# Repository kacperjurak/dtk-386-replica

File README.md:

# DTK 386 replica

This is an open source replica of the [DTK PEM-0039U](https://theretroweb.com/motherboards/s/gemlight-gmb-386umc), and its main target was to reverse engineer the pinout and functionality of the UMC 82C491 chipset, for which there are no datasheets online.

Theoretically, it should be fully functional if one were to assemble this, but I do not guarantee there won't be bugs from my side or from the original designers which made it 30+ years ago. The aim was to 100% reproduce the original PCB, with all the original components and footprints, despite the questionable trace routing in certain places.

The gerber files can be found at `/gerber`.

Special thanks to:
- Rigo for providing some useful footprints on his [retro kicad repo](https://github.com/rigred/kicad-retro)
- Sergey for some more useful footprints and symbols, from the [sandy river 486 repo](https://github.com/skiselev/sandy_river_486)

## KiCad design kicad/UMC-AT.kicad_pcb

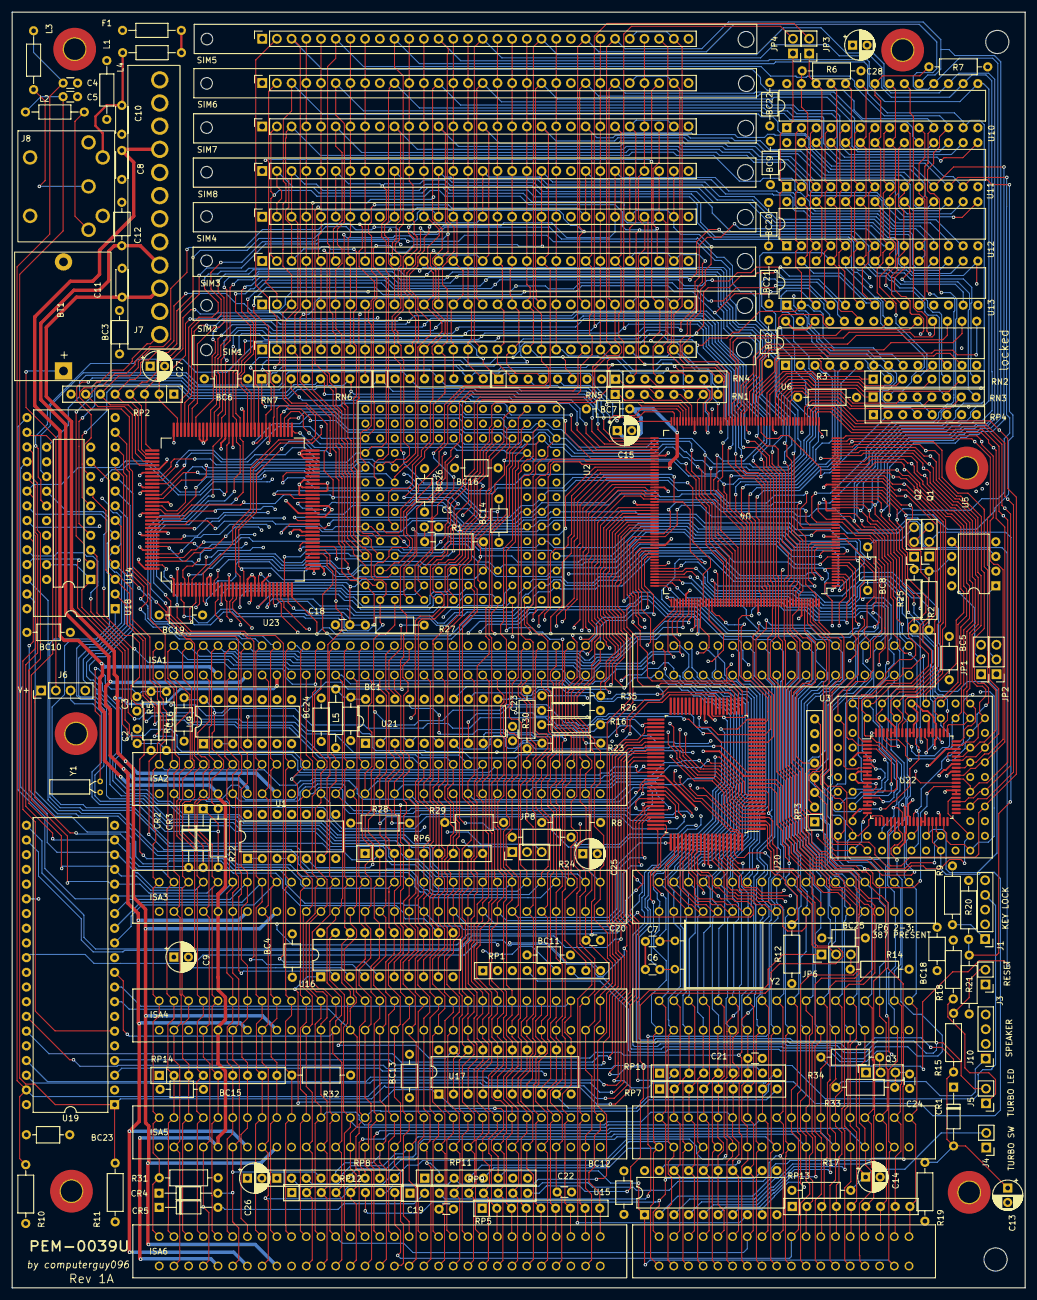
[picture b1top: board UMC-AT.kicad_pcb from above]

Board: 4 copper layers, 175.0 x 220.4 mm, 179 parts (0 on the bottom side), 337 nets.

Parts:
BC1, BC2, BC3, BC4, BC5, BC6, BC7, BC8, BC9, BC10, BC11, BC12, BC13, BC14, BC15, BC16, BC18, BC19, BC20, BC21, BC22, BC23, BC24, BC25, BC26: 100nF; C_Axial_L3.8mm_D2.6mm_P7.50mm_Horizontal
BT1: 3.6V NiCd; BATT
C1, C2, C3, C4, C5, C18, C19, C20, C21, C22, C23, C24: C; C_Disc_D3.0mm_W1.6mm_P2.50mm
C6, C7: 10pF; C_Disc_D3.0mm_W1.6mm_P2.50mm
C8, C10, C11: C; C_Disc_D4.3mm_W1.9mm_P5.00mm
C9, C13, C14, C15, C25, C26, C27, C28: 10uF; CP_Radial_D5.0mm_P2.50mm
C12, C16: C; C_Axial_L3.8mm_D2.6mm_P7.50mm_Horizontal
CR1, CR2, CR3, CR4, CR5: 1N4148; D_DO-35_SOD27_P10.16mm_Horizontal
F1: 1A; L_Axial_L5.3mm_D2.2mm_P10.16mm_Horizontal_Vishay_IM-1
H1, H2, H3, H4, H5, H6: MountingHole_Pad; MountingHole_3.7mm_Pad_TopBottom
ISA1, ISA3, ISA4, ISA5, ISA6: Bus_ISA_16bit; ISA16
ISA2: Bus_ISA_8bit; ISA8
J1: KEY LOCK; PinHeader_1x05_P2.54mm_Vertical
J3: RESET; PinHeader_1x02_P2.54mm_Vertical
J4: TURBO SW; PinHeader_1x02_P2.54mm_Vertical
J5: TURBO LED; PinHeader_1x02_P2.54mm_Vertical
J6: V+; PinHeader_1x04_P2.54mm_Vertical
J7: ATPWR
J8: KB_DIN5
J10: SPEAKER; PinHeader_1x04_P2.54mm_Vertical
JP1, JP2, JP8: PinHeader_1x03_P2.54mm_Vertical
JP3, JP4: PinHeader_1x02_P2.54mm_Vertical
JP6: 387 PRESENT; PinHeader_1x03_P2.54mm_Vertical
L1, L2, L3, L4, L5: FerriteBead; L_Axial_L5.3mm_D2.2mm_P10.16mm_Horizontal_Vishay_IM-1
Q1, Q3: 2N3904; PinSocket_1x03_P2.54mm_Vertical
Q2: 2N3906; PinSocket_1x03_P2.54mm_Vertical
R1, R2, R4, R5, R6, R7, R8, R9, R10, R11, R12, R14, R15, R16, R17, R18, R19, R20, R21, R22, R23, R24, R25, R26, R28, R29, R30, R31, R32, R33, R34, R35: R; R_Axial_DIN0207_L6.3mm_D2.5mm_P10.16mm_Horizontal
R3: 10R; R_Axial_DIN0207_L6.3mm_D2.5mm_P10.16mm_Horizontal
R27: 33R; R_Axial_DIN0207_L6.3mm_D2.5mm_P10.16mm_Horizontal
RN1, RN2, RN3, RN4, RN5, RN6, RN7: 33R; R_Array_SIP8
RP1, RP5, RP6, RP7, RP8, RP9, RP10, RP13, RP14: 4.7K; R_Array_SIP9
RP2, RP3, RP4, RP11, RP12: 4.7K; R_Array_SIP8
SIM1, SIM2, SIM3, SIM4, SIM5, SIM6, SIM7, SIM8: PinSocket_1x30_P2.54mm_Vertical
U1: 74LS00; DIP-14_W7.62mm
U2: 80386; PGA-132
U3: 80387; PGA-68
U4: 82C491; QFP-208
U5: AV9107; DIP-8_W7.62mm
U6, U10, U11, U12, U13: CY62256-70PC; DIP-28_W7.62mm
U9: 4069; DIP-14_W7.62mm
U14, U21: 74LS244; DIP-20_W7.62mm
U15, U16, U17: 74LS245; DIP-20_W7.62mm
U18: 27C512; DIP-28_W15.24mm
U19: DIP-40_W15.24mm
U20: 82C493; QFP-100
U22: Cx87DLC; LQFP-80_14x14mm_P0.65mm
U23: Am386DX; QFP-132
Y1: 32.768KHz; Crystal_C26-LF_D2.1mm_L6.5mm_Horizontal
Y2: 14.318MHz; Crystal_HC49-U_Horizontal

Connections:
+12V: C11.1, ISA1.9 (+12V), ISA2.9 (+12V), ISA3.9 (+12V), ISA4.9 (+12V), ISA5.9 (+12V), ISA6.9 (+12V), J7.10 (+12V)
-5V: C8.2, ISA1.5 (-5V), ISA2.5 (-5V), ISA3.5 (-5V), ISA4.5 (-5V), ISA5.5 (-5V), ISA6.5 (-5V), J7.4 (-5V)
-12V: C12.1, ISA1.7 (-12V), ISA2.7 (-12V), ISA3.7 (-12V), ISA4.7 (-12V), ISA5.7 (-12V), ISA6.7 (-12V), J7.9 (-12V)
/CPU/PULLUP: RP1.7 (R6), U22.27 (PULLUP)
/CPU/READYO: RP3.3 (R2), U3.L3 (~READYO)
/Cache and TAG/AA10: RN2.4 (R2.2), U10.21 (A10), U11.21 (A10), U12.21 (A10), U13.21 (A10)
/Cache and TAG/AA11: RN2.6 (R3.2), U10.23 (A11), U11.23 (A11), U12.23 (A11), U13.23 (A11)
/Cache and TAG/AA13: JP3.1, RP4.5 (R4), U6.8 (A2), U10.26 (A13), U11.26 (A13), U12.26 (A13), U13.26 (A13)
/Cache and TAG/AA14: JP4.1, RP4.4 (R3), U6.7 (A3), U10.1 (A14), U11.1 (A14), U12.1 (A14), U13.1 (A14)
/Cache and TAG/CA2: RN2.3 (R2.1), U4.71 (CA2)
/Cache and TAG/CA3A: RN2.5 (R3.1), U4.70 (CA3A)
/Cache and TAG/COEA: RN2.7 (R4.1), U4.68 (~COEA)
/Cache and TAG/CS0: RN3.4 (R2.2), U10.20 (~CS)
/Cache and TAG/CS1: RN3.6 (R3.2), U11.20 (~CS)
/Cache and TAG/CS2: RN3.8 (R4.2), U12.20 (~CS)
/Cache and TAG/CS3: R3.2, U13.20 (~CS)
/Cache and TAG/CWEA: RN3.1 (R1.1), U4.67 (~CWEA)
/Cache and TAG/OE: R7.1, RN2.8 (R4.2), U10.22 (~OE), U11.22 (~OE), U12.22 (~OE), U13.22 (~OE)
/Cache and TAG/TAG0: U4.83 (TAG0), U6.19 (Q7)
/Cache and TAG/TAG1: U4.82 (TAG1), U6.18 (Q6)
/Cache and TAG/TAG2: U4.81 (TAG2), U6.17 (Q5)
/Cache and TAG/TAG3: U4.80 (TAG3), U6.16 (Q4)
/Cache and TAG/TAG4: U4.79 (TAG4), U6.15 (Q3)
/Cache and TAG/TAG5: U4.77 (TAG5), U6.13 (Q2)
/Cache and TAG/TAG6: U4.76 (TAG6), U6.12 (Q1)
/Cache and TAG/TAG7: U4.75 (TAG7), U6.11 (Q0)
/Cache and TAG/TAGWE: RN2.1 (R1.1), U4.74 (~TAGWE)
/Cache and TAG/TWE: RN2.2 (R1.2), U6.27 (~WE)
/Cache and TAG/WE: R6.1, RN3.2 (R1.2), U10.27 (~WE), U11.27 (~WE), U12.27 (~WE), U13.27 (~WE)
/Chipset/BUFCLK: R28.2, U21.3 (O3b)
/Chipset/CHPCLK: R26.2, U4.141 (ATCLK)
/Chipset/DAC0: U4.116 (DAC0), U20.5 (DAC0)
/Chipset/DAC1: U4.114 (DAC1), U20.6 (DAC1)
/Chipset/DAC2: U4.113 (DAC2), U20.7 (DAC2)
/Chipset/FPUEN: JP6.2, U4.118 (SEL1), U20.3 (SEL1)
/Chipset/JP8/3: JP8.3, U21.16 (O1a)
/Chipset/LOWEN: R35.2, U4.130 (~LOWEN), U20.33 (~LOWEN)
/Chipset/MUXI0: U4.123 (MUXI0), U20.99 (MUXI0)
/Chipset/MUXI1: U4.121 (MUXI1), U20.100 (MUXI1)
/Chipset/MUXI2: U4.120 (MUXI2), U20.1 (MUXI2)
/Chipset/PALE: U4.143 (ALE), U21.11 (I0b)
/Chipset/POWGD: U4.129 (POWGD), U20.34 (POWGD)
/Chipset/RSTIN: U4.171 (~RSTIN), U20.29 (~RSTIN)
/Chipset/SYSCLK: C23.1, R30.1, U20.16 (SYSCLK)
/Chipset/XTL1: C6.2, U20.80 (XTL2), Y2.1
/Chipset/XTL2: C7.2, U20.79 (XTL1), Y2.2
/DRAM/A11: RN4.8 (R4.2), SIM1.24 (A11), SIM2.24 (A11), SIM3.24 (A11), SIM4.24 (A11), SIM5.24 (A11), SIM6.24 (A11), SIM7.24 (A11), SIM8.24 (A11)
/DRAM/CAS0: RN1.4 (R2.2), SIM1.2 (~CAS), SIM1.28 (~CASP), SIM5.2 (~CAS), SIM5.28 (~CASP)
/DRAM/CAS1: RN1.8 (R4.2), SIM2.2 (~CAS), SIM2.28 (~CASP), SIM6.2 (~CAS), SIM6.28 (~CASP)
/DRAM/CAS2: RN4.2 (R1.2), SIM3.2 (~CAS), SIM3.28 (~CASP), SIM7.2 (~CAS), SIM7.28 (~CASP)
/DRAM/CAS3: RN4.4 (R2.2), SIM4.2 (~CAS), SIM4.28 (~CASP), SIM8.2 (~CAS), SIM8.28 (~CASP)
/DRAM/MA0: RN7.2 (R1.2), SIM1.4 (A0), SIM2.4 (A0), SIM3.4 (A0), SIM4.4 (A0), SIM5.4 (A0), SIM6.4 (A0), SIM7.4 (A0), SIM8.4 (A0)
/DRAM/MA1: RN7.4 (R2.2), SIM1.5 (A1), SIM2.5 (A1), SIM3.5 (A1), SIM4.5 (A1), SIM5.5 (A1), SIM6.5 (A1), SIM7.5 (A1), SIM8.5 (A1)
/DRAM/MA2: RN7.6 (R3.2), SIM1.7 (A2), SIM2.7 (A2), SIM3.7 (A2), SIM4.7 (A2), SIM5.7 (A2), SIM6.7 (A2), SIM7.7 (A2), SIM8.7 (A2)
/DRAM/MA3: RN7.8 (R4.2), SIM1.8 (A3), SIM2.8 (A3), SIM3.8 (A3), SIM4.8 (A3), SIM5.8 (A3), SIM6.8 (A3), SIM7.8 (A3), SIM8.8 (A3)
/DRAM/MA4: RN6.2 (R1.2), SIM1.11 (A4), SIM2.11 (A4), SIM3.11 (A4), SIM4.11 (A4), SIM5.11 (A4), SIM6.11 (A4), SIM7.11 (A4), SIM8.11 (A4)
/DRAM/MA5: RN6.4 (R2.2), SIM1.12 (A5), SIM2.12 (A5), SIM3.12 (A5), SIM4.12 (A5), SIM5.12 (A5), SIM6.12 (A5), SIM7.12 (A5), SIM8.12 (A5)
/DRAM/MA6: RN6.6 (R3.2), SIM1.14 (A6), SIM2.14 (A6), SIM3.14 (A6), SIM4.14 (A6), SIM5.14 (A6), SIM6.14 (A6), SIM7.14 (A6), SIM8.14 (A6)
/DRAM/MA7: RN6.8 (R4.2), SIM1.15 (A7), SIM2.15 (A7), SIM3.15 (A7), SIM4.15 (A7), SIM5.15 (A7), SIM6.15 (A7), SIM7.15 (A7), SIM8.15 (A7)
/DRAM/MA8: RN5.2 (R1.2), SIM1.17 (A8), SIM2.17 (A8), SIM3.17 (A8), SIM4.17 (A8), SIM5.17 (A8), SIM6.17 (A8), SIM7.17 (A8), SIM8.17 (A8)
/DRAM/MA9: RN5.4 (R2.2), SIM1.18 (A9), SIM2.18 (A9), SIM3.18 (A9), SIM4.18 (A9), SIM5.18 (A9), SIM6.18 (A9), SIM7.18 (A9), SIM8.18 (A9)
/DRAM/MA10: RN5.6 (R3.2), SIM1.19 (A10), SIM2.19 (A10), SIM3.19 (A10), SIM4.19 (A10), SIM5.19 (A10), SIM6.19 (A10), SIM7.19 (A10), SIM8.19 (A10)
/DRAM/PA2: RN7.5 (R3.1), U4.109 (MA2), U14.2 (I0a)
/DRAM/PA3: RN7.7 (R4.1), U4.108 (MA3), U14.4 (I1a)
/DRAM/PA4: RN6.1 (R1.1), U4.107 (MA4), U14.6 (I2a)
/DRAM/PA5: RN6.3 (R2.1), U4.106 (MA5), U14.8 (I3a)
/DRAM/PA6: RN6.5 (R3.1), U4.105 (MA6), U14.11 (I0b)
/DRAM/PA7: RN6.7 (R4.1), U4.104 (MA7), U14.13 (I1b)
/DRAM/PA8: RN5.1 (R1.1), U4.103 (MA8), U14.15 (I2b)
/DRAM/PAR0: SIM1.26 (PO), SIM1.29 (PI), SIM5.26 (PO), SIM5.29 (PI), U4.88 (PAR0)
/DRAM/PAR1: SIM2.26 (PO), SIM2.29 (PI), SIM6.26 (PO), SIM6.29 (PI), U4.86 (PAR1)
/DRAM/PAR2: SIM3.26 (PO), SIM3.29 (PI), SIM7.26 (PO), SIM7.29 (PI), U4.85 (PAR2)
/DRAM/PAR3: SIM4.26 (PO), SIM4.29 (PI), SIM8.26 (PO), SIM8.29 (PI), U4.84 (PAR3)
/DRAM/RAS0: RN1.2 (R1.2), SIM1.27 (~RAS), SIM2.27 (~RAS), SIM3.27 (~RAS), SIM4.27 (~RAS)
/DRAM/RAS1: RN1.6 (R3.2), SIM5.27 (~RAS), SIM6.27 (~RAS), SIM7.27 (~RAS), SIM8.27 (~RAS)
/DRAM/WE: RN4.6 (R3.2), SIM1.21 (~WE), SIM2.21 (~WE), SIM3.21 (~WE), SIM4.21 (~WE), SIM5.21 (~WE), SIM6.21 (~WE), SIM7.21 (~WE), SIM8.21 (~WE)
/KBGND: C10.1, H1.1, J8.2 (GND), L4.1
/VBATT: BT1.1 (+), J6.2
A2: U2.C4 (A2), U3.L8 (~CMD0), U4.175 (A2), U17.9 (A7), U22.36 (~CMD0), U23.67 (A2)
A3: U2.A3, U4.176 (A3), U17.8 (A6), U23.68 (A3)
A4: U2.B3 (A4), U4.177 (A4), U6.21 (A10), U10.24 (A9), U11.24 (A9), U12.24 (A9), U13.24 (A9), U17.7 (A5), U23.69 (A4)
A5: U2.B2 (A5), U4.178 (A5), U6.23 (A11), U10.25 (A8), U11.25 (A8), U12.25 (A8), U13.25 (A8), U17.6 (A4), U23.70 (A5)
A6: U2.C3 (A6), U4.179 (A6), U6.24 (A9), U10.9 (A1), U11.9 (A1), U12.9 (A1), U13.9 (A1), U17.5 (A3), U23.71 (A6)
A7: U2.C2 (A7), U4.180 (A7), U6.25 (A8), U10.10 (A0), U11.10 (A0), U12.10 (A0), U13.10 (A0), U17.4 (A2), U23.72 (A7)
A8: U2.C1 (A8), U4.181 (A8), U6.9 (A1), U10.2 (A12), U11.2 (A12), U12.2 (A12), U13.2 (A12), U17.3 (A1), U23.74 (A8)
A9: U2.D3 (A9), U4.182 (A9), U6.10 (A0), U10.3 (A7), U11.3 (A7), U12.3 (A7), U13.3 (A7), U17.2 (A0), U23.75 (A9)
A10: U2.D2 (A10), U4.183 (A10), U6.2 (A12), U10.4 (A6), U11.4 (A6), U12.4 (A6), U13.4 (A6), U16.9 (A7), U23.76 (A10)
A11: U2.D1 (A11), U4.184 (A11), U6.3 (A7), U10.5 (A5), U11.5 (A5), U12.5 (A5), U13.5 (A5), U16.8 (A6), U23.77 (A11)
A12: U2.E3 (A12), U4.185 (A12), U6.4 (A6), U10.6 (A4), U11.6 (A4), U12.6 (A4), U13.6 (A4), U16.7 (A5), U23.78 (A12)
A13: U2.E2 (A13), U4.186 (A13), U6.5 (A5), U10.7 (A3), U11.7 (A3), U12.7 (A3), U13.7 (A3), U16.6 (A4), U23.79 (A13)
A14: U2.E1 (A14), U4.188 (A14), U6.6 (A4), U10.8 (A2), U11.8 (A2), U12.8 (A2), U13.8 (A2), U16.5 (A3), U23.81 (A14)
A15: JP4.2, U2.F1 (A15), U4.189 (A15), U16.4 (A2), U23.82 (A15)
A16: JP3.2, U2.G1 (A16), U4.190 (A16), U16.3 (A1), U23.84 (A16)
A17: U2.H1 (A17), U4.191 (A17), U16.2 (A0), U23.86 (A17)
A18: U2.H2 (A18), U4.192 (A18), U15.7 (A5), U23.87 (A18)
A19: U2.H3 (A19), U4.193 (A19), U15.6 (A4), U23.88 (A19)
A20: U2.J1 (A20), U4.194 (A20), U15.5 (A3), U23.89 (A20)
A20M: U2.F13 (~A20M), U4.1 (~A20M), U23.60 (~A20M)
A21: U2.K1 (A21), U4.196 (A21), U15.4 (A2), U23.93 (A21)
A22: U2.K2 (A22), U4.197 (A22), U15.3 (A1), U23.94 (A22)
A23: U2.L1 (A23), U4.198 (A23), U15.2 (A0), U23.95 (A23)
A24: U2.L2 (A24), U4.199 (A24), U23.96 (A24)
A25: U2.K3 (A25), U4.200 (A25), U23.97 (A25)
A26: RP2.2 (R1), U2.M1 (A26), U23.98 (A26)
A27: RP2.3 (R2), U2.N1 (A27), U23.100 (A27)
A28: RP2.4 (R3), U2.L3 (A28), U23.101 (A28)
A29: RP2.5 (R4), U2.M2 (A29), U23.102 (A29)
A30: RP2.6 (R5), U2.P1 (A30), U23.103 (A30)
A31: RP2.7 (R6), U2.N2 (A31), U3.K6 (NPS2), U4.201 (A31), U22.32 (NPS2), U23.104 (A31)
ADS: RP1.6 (R5), U2.E14 (~ADS), U3.K7 (~ADS), U4.7 (~ADS), U22.35 (~ADS), U23.27 (~ADS)
AEN: ISA1.42 (AEN), ISA2.42 (AEN), ISA3.42 (AEN), ISA4.42 (AEN), ISA5.42 (AEN), ISA6.42 (AEN), U20.65 (AEN)
ALE: C22.2, ISA1.28 (ALE), ISA2.28 (ALE), ISA3.28 (ALE), ISA4.28 (ALE), ISA5.28 (ALE), ISA6.28 (ALE), U21.9 (O0b)
ATCLK: C19.2, ISA1.20 (CLK), ISA2.20 (CLK), ISA3.20 (CLK), ISA4.20 (CLK), ISA5.20 (CLK), ISA6.20 (CLK), R29.1
BA0: ISA1.62 (BA00), ISA2.62 (BA00), ISA3.62 (BA00), ISA4.62 (BA00), ISA5.62 (BA00), ISA6.62 (BA00), RP5.9 (R8), U4.146 (A0), U18.10 (A0)
BA1: ISA1.61 (BA01), ISA2.61 (BA01), ISA3.61 (BA01), ISA4.61 (BA01), ISA5.61 (BA01), ISA6.61 (BA01), RP5.8 (R7), U4.145 (A1), U18.9 (A1)
BA2: ISA1.60 (BA02), ISA2.60 (BA02), ISA3.60 (BA02), ISA4.60 (BA02), ISA5.60 (BA02), ISA6.60 (BA02), RP5.7 (R6), U14.18 (O0a), U17.11 (B7), U18.8 (A2), U19.9 (A2)
BA3: ISA1.59 (BA03), ISA2.59 (BA03), ISA3.59 (BA03), ISA4.59 (BA03), ISA5.59 (BA03), ISA6.59 (BA03), RP5.6 (R5), U14.16 (O1a), U17.12 (B6), U18.7 (A3)
BA4: ISA1.58 (BA04), ISA2.58 (BA04), ISA3.58 (BA04), ISA4.58 (BA04), ISA5.58 (BA04), ISA6.58 (BA04), RP5.5 (R4), U14.14 (O2a), U17.13 (B5), U18.6 (A4)
BA5: ISA1.57 (BA05), ISA2.57 (BA05), ISA3.57 (BA05), ISA4.57 (BA05), ISA5.57 (BA05), ISA6.57 (BA05), RP5.4 (R3), U14.12 (O3a), U17.14 (B4), U18.5 (A5)
BA6: ISA1.56 (BA06), ISA2.56 (BA06), ISA3.56 (BA06), ISA4.56 (BA06), ISA5.56 (BA06), ISA6.56 (BA06), RP5.3 (R2), U14.9 (O0b), U17.15 (B3), U18.4 (A6)
BA7: ISA1.55 (BA07), ISA2.55 (BA07), ISA3.55 (BA07), ISA4.55 (BA07), ISA5.55 (BA07), ISA6.55 (BA07), RP5.2 (R1), U14.7 (O1b), U17.16 (B2), U18.3 (A7)
BA8: ISA1.54 (BA08), ISA2.54 (BA08), ISA3.54 (BA08), ISA4.54 (BA08), ISA5.54 (BA08), ISA6.54 (BA08), RP6.9 (R8), U14.5 (O2b), U17.17 (B1), U18.25 (A8)
BA9: ISA1.53 (BA09), ISA2.53 (BA09), ISA3.53 (BA09), ISA4.53 (BA09), ISA5.53 (BA09), ISA6.53 (BA09), RP6.8 (R7), U17.18 (B0), U18.24 (A9)
BA10: ISA1.52 (BA10), ISA2.52 (BA10), ISA3.52 (BA10), ISA4.52 (BA10), ISA5.52 (BA10), ISA6.52 (BA10), RP6.7 (R6), U16.11 (B7), U18.21 (A10)
BA11: ISA1.51 (BA11), ISA2.51 (BA11), ISA3.51 (BA11), ISA4.51 (BA11), ISA5.51 (BA11), ISA6.51 (BA11), RP6.6 (R5), U16.12 (B6), U18.23 (A11)
BA12: ISA1.50 (BA12), ISA2.50 (BA12), ISA3.50 (BA12), ISA4.50 (BA12), ISA5.50 (BA12), ISA6.50 (BA12), RP6.5 (R4), U16.13 (B5), U18.2 (A12)
BA13: ISA1.49 (BA13), ISA2.49 (BA13), ISA3.49 (BA13), ISA4.49 (BA13), ISA5.49 (BA13), ISA6.49 (BA13), RP6.4 (R3), U16.14 (B4), U18.26 (A13)
BA14: ISA1.48 (BA14), ISA2.48 (BA14), ISA3.48 (BA14), ISA4.48 (BA14), ISA5.48 (BA14), ISA6.48 (BA14), RP6.3 (R2), U16.15 (B3), U18.27 (A14)
BA15: ISA1.47 (BA15), ISA2.47 (BA15), ISA3.47 (BA15), ISA4.47 (BA15), ISA5.47 (BA15), ISA6.47 (BA15), RP6.2 (R1), U16.16 (B2), U18.1 (A15)
BA16: ISA1.46 (BA16), ISA2.46 (BA16), ISA3.46 (BA16), ISA4.46 (BA16), ISA5.46 (BA16), ISA6.46 (BA16), RP7.9 (R8), U16.17 (B1)
BA17: ISA1.45 (BA17), ISA1.88 (LA17), ISA2.45 (BA17), ISA3.45 (BA17), ISA3.88 (LA17), ISA4.45 (BA17), ISA4.88 (LA17), ISA5.45 (BA17), ISA5.88 (LA17), ISA6.45 (BA17), ISA6.88 (LA17), RP7.8 (R7), U16.18 (B0)
BA18: ISA1.44 (BA18), ISA1.87 (LA18), ISA2.44 (BA18), ISA3.44 (BA18), ISA3.87 (LA18), ISA4.44 (BA18), ISA4.87 (LA18), ISA5.44 (BA18), ISA5.87 (LA18), ISA6.44 (BA18), ISA6.87 (LA18), RP7.7 (R6), U15.13 (B5)
BA19: ISA1.43 (BA19), ISA1.86 (LA19), ISA2.43 (BA19), ISA3.43 (BA19), ISA3.86 (LA19), ISA4.43 (BA19), ISA4.86 (LA19), ISA5.43 (BA19), ISA5.86 (LA19), ISA6.43 (BA19), ISA6.86 (LA19), RP7.6 (R5), U14.3 (O3b), U15.14 (B4)
BA20: ISA1.85 (LA20), ISA3.85 (LA20), ISA4.85 (LA20), ISA5.85 (LA20), ISA6.85 (LA20), RP7.5 (R4), U15.15 (B3)
BA21: ISA1.84 (LA21), ISA3.84 (LA21), ISA4.84 (LA21), ISA5.84 (LA21), ISA6.84 (LA21), RP7.4 (R3), U15.16 (B2)
BA22: ISA1.83 (LA22), ISA3.83 (LA22), ISA4.83 (LA22), ISA5.83 (LA22), ISA6.83 (LA22), RP7.3 (R2), U15.17 (B1)
BA23: ISA1.82 (LA23), ISA3.82 (LA23), ISA4.82 (LA23), ISA5.82 (LA23), ISA6.82 (LA23), RP7.2 (R1), U15.18 (B0)
BE0: U2.E12 (~BE0), U4.13 (~BE0), U23.31 (~BE0)
BE1: U2.C13 (~BE1), U4.14 (~BE1), U23.32 (~BE1)
BE2: U2.B13 (~BE2), U4.15 (~BE2), U23.33 (~BE2)
BE3: U2.A13 (~BE3), U4.16 (~BE3), U23.38 (~BE3)
BHE: U4.144 (~BHE), U15.8 (A6)
BLAST: RP3.2 (R1), U4.204 (~BLAST)
BS16: RP1.9 (R8), U2.C14 (~BS16), U23.29 (~BS16)
BUSY: U2.B9 (~BUSY), U4.3 (~PEADS), U23.46 (~BUSY)
CLK: R2.2, R25.2, U5.6 (CLK)
CLK2: C18.2, R1.1, R27.1, U2.F12 (CLK2), U23.24 (CLK2)
CLKRTC: U4.170 (XTL1), U9.4
D0: SIM1.3 (D0), SIM5.3 (D0), U2.H12 (D0), U3.H2 (D0), U4.23 (PD0), U10.11 (Q0), U22.2 (D0), U23.20 (D0)
D1: SIM1.6 (D1), SIM5.6 (D1), U2.H13 (D1), U3.H1 (D1), U4.24 (PD1), U10.12 (Q1), U22.3 (D1), U23.19 (D1)
D2: SIM1.10 (D2), SIM5.10 (D2), U2.H14 (D2), U3.G2 (D2), U4.25 (PD2), U10.13 (Q2), U22.7 (D2), U23.18 (D2)
D3: SIM1.13 (D3), SIM5.13 (D3), U2.J14 (D3), U3.G1 (D3), U4.26 (PD3), U10.15 (Q3), U22.69 (D3), U23.17 (D3)
D4: SIM1.16 (D4), SIM5.16 (D4), U2.K14 (D4), U3.D2 (D4), U4.28 (PD4), U10.16 (Q4), U22.68 (D4), U23.15 (D4)
D5: SIM1.20 (D5), SIM5.20 (D5), U2.K13 (D5), U3.D1 (D5), U4.29 (PD5), U10.17 (Q5), U22.67 (D5), U23.14 (D5)
D6: SIM1.23 (D6), SIM5.23 (D6), U2.L14 (D6), U3.C2 (D6), U4.30 (PD6), U10.18 (Q6), U22.63 (D6), U23.13 (D6)
D7: SIM1.25 (D7), SIM5.25 (D7), U2.K12 (D7), U3.C1 (D7), U4.31 (PD7), U10.19 (Q7), U22.62 (D7), U23.12 (D7)
D8: SIM2.3 (D0), SIM6.3 (D0), U2.L13 (D8), U3.B1 (D8), U4.32 (PD8), U11.11 (Q0), U22.8 (D8), U23.9 (D8)
D9: SIM2.6 (D1), SIM6.6 (D1), U2.N14 (D9), U3.A2 (D9), U4.33 (PD9), U11.12 (Q1), U22.14 (D9), U23.7 (D9)
D10: SIM2.10 (D2), SIM6.10 (D2), U2.M12 (D10), U3.B3 (D10), U4.34 (PD10), U11.13 (Q2), U22.15 (D10), U23.6 (D10)
D11: SIM2.13 (D3), SIM6.13 (D3), U2.N13 (D11), U3.A3 (D11), U4.35 (PD11), U11.15 (Q3), U22.16 (D11), U23.5 (D11)
D12: SIM2.16 (D4), SIM6.16 (D4), U2.N12 (D12), U3.A4 (D12), U4.37 (PD12), U11.16 (Q4), U22.79 (D12), U23.4 (D12)
D13: SIM2.20 (D5), SIM6.20 (D5), U2.P13 (D13), U3.B5 (D13), U4.38 (PD13), U11.17 (Q5), U22.78 (D13), U23.3 (D13)
D14: SIM2.23 (D6), SIM6.23 (D6), U2.P12 (D14), U3.A5 (D14), U4.39 (PD14), U11.18 (Q6), U22.74 (D14), U23.131 (D14)
D15: SIM2.25 (D7), SIM6.25 (D7), U2.M11 (D15), U3.B6 (D15), U4.40 (PD15), U11.19 (Q7), U22.73 (D15), U23.130 (D15)
D16: SIM3.3 (D0), SIM7.3 (D0), U2.N11 (D16), U3.A7 (D16), U4.41 (PD16), U12.11 (Q0), U22.1 (D16), U23.129 (D16)
D17: SIM3.6 (D1), SIM7.6 (D1), U2.N10 (D17), U3.B8 (D17), U4.42 (PD17), U12.12 (Q1), U22.72 (D17), U23.128 (D17)
D18: SIM3.10 (D2), SIM7.10 (D2), U2.P11 (D18), U3.A8 (D18), U4.43 (PD18), U12.13 (Q2), U22.80 (D18), U23.126 (D18)
D19: SIM3.13 (D3), SIM7.13 (D3), U2.P10 (D19), U3.B9 (D19), U4.44 (PD19), U12.15 (Q3), U22.77 (D19), U23.125 (D19)
D20: SIM3.16 (D4), SIM7.16 (D4), U2.M9 (D20), U3.B10 (D20), U4.46 (PD20), U12.16 (Q4), U22.61 (D20), U23.124 (D20)
D21: SIM3.20 (D5), SIM7.20 (D5), U2.N9 (D21), U3.A10 (D21), U4.47 (PD21), U12.17 (Q5), U22.60 (D21), U23.121 (D21)
D22: SIM3.23 (D6), SIM7.23 (D6), U2.P9 (D22), U3.B11 (D22), U4.48 (PD22), U12.18 (Q6), U22.59 (D22), U23.120 (D22)
D23: SIM3.25 (D7), SIM7.25 (D7), U2.N8 (D23), U3.C10 (D23), U4.49 (PD23), U12.19 (Q7), U22.57 (D23), U23.119 (D23)
D24: SIM4.3 (D0), SIM8.3 (D0), U2.P7 (D24), U3.D10 (D24), U4.50 (PD24), U13.11 (Q0), U22.56 (D24), U23.118 (D24)
D25: SIM4.6 (D1), SIM8.6 (D1), U2.N6 (D25), U3.D11 (D25), U4.51 (PD25), U13.12 (Q1), U22.55 (D25), U23.116 (D25)
D26: SIM4.10 (D2), SIM8.10 (D2), U2.P5 (D26), U3.E10 (D26), U4.52 (PD26), U13.13 (Q2), U22.53 (D26), U23.115 (D26)
D27: SIM4.13 (D3), SIM8.13 (D3), U2.N5 (D27), U3.E11 (D27), U4.54 (PD27), U13.15 (Q3), U22.51 (D27), U23.113 (D27)
D28: SIM4.16 (D4), SIM8.16 (D4), U2.M6 (D28), U3.G10 (D28), U4.55 (PD28), U13.16 (Q4), U22.50 (D28), U23.112 (D28)
D29: SIM4.20 (D5), SIM8.20 (D5), U2.P4 (D29), U3.G11 (D29), U4.56 (PD29), U13.17 (Q5), U22.44 (D29), U23.109 (D29)
D30: SIM4.23 (D6), SIM8.23 (D6), U2.P3 (D30), U3.H10 (D30), U4.57 (PD30), U13.18 (Q6), U22.42 (D30), U23.108 (D30)
D31: SIM4.25 (D7), SIM8.25 (D7), U2.M5 (D31), U3.H11 (D31), U4.58 (PD31), U13.19 (Q7), U22.25 (D31), U23.107 (D31)
DACK0: ISA1.70 (~DACK0), ISA3.70 (~DACK0), ISA4.70 (~DACK0), ISA5.70 (~DACK0), ISA6.70 (~DACK0), U20.11 (~DACK0)
DACK1: ISA1.17 (~DACK1), ISA2.17 (~DACK1), ISA3.17 (~DACK1), ISA4.17 (~DACK1), ISA5.17 (~DACK1), ISA6.17 (~DACK1), U20.9 (~DACK1)
DACK2: ISA1.26 (~DACK2), ISA2.26 (~DACK2), ISA3.26 (~DACK2), ISA4.26 (~DACK2), ISA5.26 (~DACK2), ISA6.26 (~DACK2), U20.10 (~DACK2)
DACK3: ISA1.15 (~DACK3), ISA2.15 (~DACK3), ISA3.15 (~DACK3), ISA4.15 (~DACK3), ISA5.15 (~DACK3), ISA6.15 (~DACK3), U20.8 (~DACK3)
DACK5: ISA1.72 (~DACK5), ISA3.72 (~DACK5), ISA4.72 (~DACK5), ISA5.72 (~DACK5), ISA6.72 (~DACK5), U20.12 (~DACK5)
DACK6: ISA1.74 (~DACK6), ISA3.74 (~DACK6), ISA4.74 (~DACK6), ISA5.74 (~DACK6), ISA6.74 (~DACK6), U20.13 (~DACK6)
DACK7: ISA1.76 (~DACK7), ISA3.76 (~DACK7), ISA4.76 (~DACK7), ISA5.76 (~DACK7), ISA6.76 (~DACK7), U20.14 (~DACK7)
DRQ0: ISA1.71 (DRQ0), ISA3.71 (DRQ0), ISA4.71 (DRQ0), ISA5.71 (DRQ0), ISA6.71 (DRQ0), RP8.2 (R1), U20.89 (DRQ0)
DRQ1: ISA1.18 (DRQ1), ISA2.18 (DRQ1), ISA3.18 (DRQ1), ISA4.18 (DRQ1), ISA5.18 (DRQ1), ISA6.18 (DRQ1), RP8.3 (R2), U20.72 (DRQ1)
DRQ2: CR4.2 (A), ISA1.6 (DRQ2), ISA2.6 (DRQ2), ISA3.6 (DRQ2), ISA4.6 (DRQ2), ISA5.6 (DRQ2), ISA6.6 (DRQ2), RP8.4 (R3), U20.68 (DRQ2)
DRQ3: ISA1.16 (DRQ3), ISA2.16 (DRQ3), ISA3.16 (DRQ3), ISA4.16 (DRQ3), ISA5.16 (DRQ3), ISA6.16 (DRQ3), RP8.5 (R4), U20.71 (DRQ3)
DRQ5: ISA1.73 (DRQ5), ISA3.73 (DRQ5), ISA4.73 (DRQ5), ISA5.73 (DRQ5), ISA6.73 (DRQ5), RP8.6 (R5), U20.92 (DRQ5)
DRQ6: ISA1.75 (DRQ6), ISA3.75 (DRQ6), ISA4.75 (DRQ6), ISA5.75 (DRQ6), ISA6.75 (DRQ6), RP8.7 (R6), U20.93 (DRQ6)
DRQ7: ISA1.77 (DRQ7), ISA3.77 (DRQ7), ISA4.77 (DRQ7), ISA5.77 (DRQ7), ISA6.77 (DRQ7), RP8.8 (R7), U20.94 (DRQ7)
D/C: U2.A11 (D/~C), U4.12 (D/~C), U23.41 (D/~C)
ELBA: RP3.6 (R5), U4.8 (~ELBA)
FERR: RP3.8 (R7), U3.L2 (~ERROR), U4.2 (~FERR), U22.20 (~ERROR)
FERROR: RP3.7 (R6), U2.A8 (~ERROR), U4.4 (~IGNNE), U23.47 (~ERROR)
FLUSH: U1.6, U2.E13 (~FLUSH), U23.39 (~FLUSH)
GND: BC1.1, BC2.2, BC3.2, BC4.2, BC5.2, BC6.2, BC7.1, BC8.1, BC9.2, BC10.2, BC11.2, BC12.2, BC13.2, BC14.2, BC15.2, BC16.2, BC18.2, BC19.2, BC20.2, BC21.2, BC22.2, BC23.2, BC24.2, BC25.2, BC26.2, BT1.2 (-), C1.2, C2.2, C3.1, C4.2, C5.2, C6.1, C7.1, C8.1, C9.2, C11.2, C12.2, C13.2, C14.2, C15.2, C16.1, C18.1, C19.1, C20.2, C21.1, C22.1, C23.2, C24.1, C25.2, C26.2, C27.2, C28.2, CR4.1 (K), CR5.1 (K), H2.1, H3.1, H4.1, H5.1, H6.1, ISA1.1 (GND), ISA1.10 (GND), ISA1.31 (GND), ISA1.80 (GND), ISA2.1 (GND), ISA2.10 (GND), ISA2.31 (GND), ISA3.1 (GND), ISA3.10 (GND), ISA3.31 (GND), ISA3.80 (GND), ISA4.1 (GND), ISA4.10 (GND), ISA4.31 (GND), ISA4.80 (GND), ISA5.1 (GND), ISA5.10 (GND), ISA5.31 (GND), ISA5.80 (GND), ISA6.1 (GND), ISA6.10 (GND), ISA6.31 (GND), ISA6.80 (GND), J1.2, J1.3, J1.5, J3.1, J4.1, J6.4, J7.5 (GND), J7.6 (GND), J7.7 (GND), J7.8 (GND), J10.3, JP1.3, JP2.3, L4.2, Q1.1 (E), Q3.1 (E), R6.2, R7.2, R10.1, R11.1, R14.2, R20.2, R35.1, RP2.1 (common), RP8.1 (common), SIM1.9 (GND), SIM1.22 (GND), SIM2.9 (GND), SIM2.22 (GND), SIM3.9 (GND), SIM3.22 (GND), SIM4.9 (GND), SIM4.22 (GND), SIM5.9 (GND), SIM5.22 (GND), SIM6.9 (GND), SIM6.22 (GND), SIM7.9 (GND), SIM7.22 (GND), SIM8.9 (GND), SIM8.22 (GND), U1.7 (GND), U2.A2 (VSS), U2.A6 (VSS), U2.A9 (VSS), U2.B1 (VSS), U2.B5 (VSS), U2.B11 (VSS), U2.B14 (VSS), U2.C11 (VSS), U2.F2 (VSS), U2.F3 (VSS), U2.F14 (VSS), U2.J2 (VSS), U2.J3 (VSS), U2.J12 (VSS), U2.J13 (VSS), U2.M4 (VSS), U2.M8 (VSS), U2.M10 (VSS), U2.N3 (VSS), U2.P6 (VSS), U2.P14 (VSS), U3.B2 (VSS), U3.B7 (VSS), U3.C11 (VSS), U3.E2 (VSS), U3.F2 (VSS), U3.F11 (VSS), U3.J1 (VSS), U3.J10 (VSS), U3.L5 (VSS), U4.18 (GND), U4.27 (GND), U4.36 (GND), U4.59 (GND), U4.69 (GND), U4.87 (GND), U4.96 (GND), U4.111 (GND), U4.122 (GND), U4.128 (GND), U4.142 (GND), U4.162 (GND), U4.187 (GND), U4.202 (GND), U5.2 (GND), U6.14 (GND), U6.20 (~CS), U6.22 (~OE), U9.5, U9.7 (VSS), U9.9, U9.11, U9.13, U10.14 (GND), U11.14 (GND), U12.14 (GND), U13.14 (GND), U14.10 (GND), U14.17 (I3b), U15.10 (GND), U16.10 (GND), U17.10 (GND), U18.14 (GND), U19.2 (XTAL1), U19.7 (EA), U19.20 (GND), U20.15 (GND), U20.40 (GND), U20.66 (GND), U20.78 (GND), U20.90 (GND), U21.1 (OEa), U21.10 (GND), U21.19 (OEb), U22.4 (VSS), U22.9 (VSS), U22.10 (VSS), U22.12 (VSS), U22.13 (VSS), U22.17 (VSS), U22.18 (VSS), U22.29 (VSS), U22.46 (VSS), U22.47 (VSS), U22.52 (VSS), U22.58 (VSS), U22.65 (VSS), U22.66 (VSS), U23.1 (VSS), U23.10 (VSS), U23.11 (VSS), U23.21 (VSS), U23.23 (VSS), U23.25 (VSS), U23.35 (VSS), U23.44 (VSS), U23.48 (VSS), U23.51 (VSS), U23.55 (VSS), U23.57 (VSS), U23.64 (VSS), U23.65 (VSS), U23.66 (VSS), U23.80 (VSS), U23.83 (VSS), U23.90 (VSS), U23.91 (VSS), U23.92 (VSS), U23.105 (VSS), U23.111 (VSS), U23.114 (VSS), U23.122 (VSS), U23.132 (VSS)
HLDA: U1.5, U2.M14 (HLDA), U4.9 (HLDA), U20.24 (HLDA), U23.8 (HLDA)
HOLD: U2.D14 (HOLD), U4.19 (HOLD), U20.26 (HOLD), U23.28 (HOLD)
INTR: U2.B7 (INTR), U4.21 (INTR), U23.53 (INTR)
IOCK: ISA1.32 (IO), ISA2.32 (IO), ISA3.32 (IO), ISA4.32 (IO), ISA5.32 (IO), ISA6.32 (IO), R31.1, U20.64 (~I/OCHCK)
IOCS: ISA1.64 (~IOCS16), ISA3.64 (~IOCS16), ISA4.64 (~IOCS16), ISA5.64 (~IOCS16), ISA6.64 (~IOCS16), RP11.4 (R3), U4.134 (~IOCS16)
IOR: ISA1.14 (~IOR), ISA2.14 (~IOR), ISA3.14 (~IOR), ISA4.14 (~IOR), ISA5.14 (~IOR), ISA6.14 (~IOR), RP12.5 (R4), U4.132 (~IOR), U19.8 (~RD)
IORDY: ISA1.41 (IO_READY), ISA2.41 (IO_READY), ISA3.41 (IO_READY), ISA4.41 (IO_READY), ISA5.41 (IO_READY), ISA6.41 (IO_READY), R32.1, U4.125 (IOCHRDY)
IOW: ISA1.13 (~IOW), ISA2.13 (~IOW), ISA3.13 (~IOW), ISA4.13 (~IOW), ISA5.13 (~IOW), ISA6.13 (~IOW), RP12.4 (R3), U4.131 (~IOW), U19.10 (~WR)
IRQ2: CR5.2 (A), ISA1.4 (IRQ2), ISA2.4 (IRQ2), ISA3.4 (IRQ2), ISA4.4 (IRQ2), ISA5.4 (IRQ2), ISA6.4 (IRQ2), RP9.2 (R1), U20.67 (IRQ2)
IRQ3: ISA1.25 (IRQ3), ISA2.25 (IRQ3), ISA3.25 (IRQ3), ISA4.25 (IRQ3), ISA5.25 (IRQ3), ISA6.25 (IRQ3), RP9.8 (R7), U20.81 (IRQ3)
IRQ4: ISA1.24 (IRQ4), ISA2.24 (IRQ4), ISA3.24 (IRQ4), ISA4.24 (IRQ4), ISA5.24 (IRQ4), ISA6.24 (IRQ4), RP9.7 (R6), U20.77 (IRQ4)
IRQ5: ISA1.23 (IRQ5), ISA2.23 (IRQ5), ISA3.23 (IRQ5), ISA4.23 (IRQ5), ISA5.23 (IRQ5), ISA6.23 (IRQ5), RP9.6 (R5), U20.76 (IRQ5)
IRQ6: ISA1.22 (IRQ6), ISA2.22 (IRQ6), ISA3.22 (IRQ6), ISA4.22 (IRQ6), ISA5.22 (IRQ6), ISA6.22 (IRQ6), RP9.5 (R4), U20.75 (IRQ6)
IRQ7: ISA1.21 (IRQ7), ISA2.21 (IRQ7), ISA3.21 (IRQ7), ISA4.21 (IRQ7), ISA5.21 (IRQ7), ISA6.21 (IRQ7), RP9.4 (R3), U20.74 (IRQ7)
IRQ10: ISA1.65 (IRQ10), ISA3.65 (IRQ10), ISA4.65 (IRQ10), ISA5.65 (IRQ10), ISA6.65 (IRQ10), RP10.3 (R2), U20.82 (IRQ10)
IRQ11: ISA1.66 (IRQ11), ISA3.66 (IRQ11), ISA4.66 (IRQ11), ISA5.66 (IRQ11), ISA6.66 (IRQ11), RP10.4 (R3), U20.83 (IRQ11)
IRQ12: ISA1.67 (IRQ12), ISA3.67 (IRQ12), ISA4.67 (IRQ12), ISA5.67 (IRQ12), ISA6.67 (IRQ12), RP10.5 (R4), U20.84 (IRQ12)
IRQ14: C21.2, ISA1.69 (IRQ14), ISA3.69 (IRQ14), ISA4.69 (IRQ14), ISA5.69 (IRQ14), ISA6.69 (IRQ14), RP10.7 (R6), U20.86 (IRQ14)
IRQ15: ISA1.68 (IRQ15), ISA3.68 (IRQ15), ISA4.68 (IRQ15), ISA5.68 (IRQ15), ISA6.68 (IRQ15), RP10.6 (R5), U20.85 (IRQ15)
KBCI: C5.1, L2.2, R11.2, U19.1 (KBCI), U20.62 (KBCT0)
KBCLK: R8.2, U4.167 (KBCLK)
KBCO: U19.37 (KBCO), U20.59 (KBCP26)
KBCP13: U19.30 (P13), U20.38 (KBCP13)
KBCP21: RP10.9 (R8), U19.22 (~GA20), U20.58 (KBCP21)
KBCP24: RP10.8 (R7), U19.21 (~RC), U20.57 (KBCP24)
KBCRST: U19.4 (~RESET), U20.53 (KBCRST)
KBDI: C4.1, L3.2, R10.2, U19.39 (KBDI/MSCI), U20.61 (KBCT1)
KBDO: U19.38 (KBDO), U20.60 (KBCP27)
KBIRQ1: U19.35 (IRQ1), U20.56 (KBCIRQ)
KBLOCK: J1.4, U19.34 (~KBD_INH)
KEN: U4.208 (~READYO/~KEN), U22.49 (KEN)
LOCK: U3.K1 (PEREQ), U4.205 (FPEREQ/~LOCK), U22.48 (PEREQ)
MASTER: ISA1.79 (MASTER), ISA3.79 (MASTER), ISA4.79 (MASTER), ISA5.79 (MASTER), ISA6.79 (MASTER), RP11.6 (R5), U4.137 (~MASTER), U15.1 (A->B), U16.1 (A->B), U17.1 (A->B), U20.95 (~MASTER)
MEMCS: ISA1.63 (~MEMCS16), ISA3.63 (~MEMCS16), ISA4.63 (~MEMCS16), ISA5.63 (~MEMCS16), ISA6.63 (~MEMCS16), RP11.5 (R4), U4.133 (~MEMCS16)
MEMR: ISA1.89 (~MEMR), ISA3.89 (~MEMR), ISA4.89 (~MEMR), ISA5.89 (~MEMR), ISA6.89 (~MEMR), RP12.7 (R6), U4.127 (~MEMR), U18.22 (~OE), U20.87 (~MEMR16)
MEMW: ISA1.90 (~MEMW), ISA3.90 (~MEMW), ISA4.90 (~MEMW), ISA5.90 (~MEMW), ISA6.90 (~MEMW), RP12.8 (R7), U1.1, U1.2, U4.126 (~MEMW), U20.88 (~MEMR16)
M/IO: U2.A12 (M/~IO), U3.L6 (~NPS1), U4.11 (M/~IO), U22.31 (~NPS1), U23.40 (M/~IO)
NA: RP1.8 (R7), U2.D13 (~NA), U23.30 (~NA)
NCLK: R24.2, U3.K10 (CPUCLK), U22.45 (CPUCLK)
NMI: U2.B8 (NMI), U4.22 (NMI), U23.52 (NMI)
unnamed: C1.1, R1.2
unnamed: C2.1, R4.2, U9.1, Y1.2
unnamed: C3.2, R4.1, R5.1, Y1.1
unnamed: CR2.2 (A), J6.1
unnamed: CR2.1 (K), CR3.2 (A)
unnamed: CR3.1 (K), J6.3, R22.1
unnamed: F1.2, L1.1
unnamed: J1.1, R9.1
unnamed: J3.2, R15.2
unnamed: J5.1, R18.1
unnamed: J8.1 (CLK), L2.1
unnamed: J8.3 (DATA), L3.1
unnamed: C10.2, J8.4 (VCC), L1.2
unnamed: J10.1, R33.1
unnamed: JP1.2, U5.5 (FS1)
unnamed: JP2.2, U5.1 (FS0)
unnamed: JP6.1, RP10.2 (R1)
unnamed: JP6.3, R14.1
unnamed: JP8.1, R25.1, U21.17 (I3b)
unnamed: JP8.2, R24.1
unnamed: Q1.2 (B), R20.1, R21.2
unnamed: Q1.3 (C), Q2.2 (B)
unnamed: Q3.2 (B), R34.2
unnamed: C24.2, Q3.3 (C), R33.2
unnamed: R5.2, U9.2, U9.3
unnamed: RN1.1 (R1.1), U4.99 (~RAS0)
unnamed: RN1.3 (R2.1), U4.98 (~CAS0)
unnamed: RN1.5 (R3.1), U4.97 (~RAS1)
unnamed: RN1.7 (R4.1), U4.95 (~CAS1)
unnamed: RN3.3 (R2.1), U4.66 (~CSEL0)
unnamed: RN3.5 (R3.1), U4.65 (~CSEL1)
unnamed: RN3.7 (R4.1), U4.64 (~CSEL2)
unnamed: RN4.1 (R1.1), U4.93 (~CAS2)
unnamed: RN4.3 (R2.1), U4.91 (~CAS3)
unnamed: RN4.5 (R3.1), U4.90 (~MWE)
unnamed: RN4.7 (R4.1), U4.92 (~RAS3)
unnamed: RN5.3 (R2.1), U4.101 (MA9)
unnamed: RN5.5 (R3.1), U4.100 (MA10)
unnamed: RN7.1 (R1.1), U4.112 (MA0)
unnamed: RN7.3 (R2.1), U4.110 (MA1)
unnamed: RP4.2 (R1), U4.73 (ALT)
unnamed: U1.3, U1.4
unnamed: R3.1, U4.63 (~CSEL3)
unnamed: R2.1, U4.172 (CLKIN)
unnamed: R8.1, U19.3 (XTAL2)
unnamed: R28.1, U21.2 (I0a), U21.4 (I1a), U21.6 (I2a)
unnamed: R26.1, U21.8 (I3a)
unnamed: R27.2, U21.18 (O0a)
unnamed: R23.1, U21.7 (O1b)
unnamed: R30.2, U21.14 (O2a)
unnamed: R29.2, U21.12 (O3a)
unnamed: BC1.2, L5.2, U21.20 (VCC)
OSC: C20.1, ISA1.30 (OSC), ISA2.30 (OSC), ISA3.30 (OSC), ISA4.30 (OSC), ISA5.30 (OSC), ISA6.30 (OSC), R23.2
PCD: RP1.4 (R3), U3.K2 (~BUSY), U4.206 (~FBUSY/PCD), U22.23 (~BUSY)
PEREQ: U2.C8 (PEREQ), U4.207 (PEREQ/~BRDY), U23.50 (PEREQ)
PWRGD: J7.12 (PWRGD), R16.2, U20.52 (PWRGD)
READY: RP3.4 (R3), U2.G13 (~READY), U3.K8 (~READY), U4.17 (~READY), U22.37 (~READY), U23.26 (~READY)
REFSH: U15.19 (CE), U16.19 (CE), U17.19 (CE), U20.96 (REFRESH)
RESET: ISA1.2 (RESET), ISA2.2 (RESET), ISA3.2 (RESET), ISA4.2 (RESET), ISA5.2 (RESET), ISA6.2 (RESET), U21.5 (O2b)
RFSH: ISA1.19 (~REFRESH), ISA2.19 (~DACK0), ISA3.19 (~REFRESH), ISA4.19 (~REFRESH), ISA5.19 (~REFRESH), ISA6.19 (~REFRESH), RP11.2 (R1), U4.136 (~REFRESH), U14.1 (OEa), U14.19 (OEb), U20.73 (~REFRESH)
ROMCS: U4.168 (~ROMCS), U18.20 (~CE), U19.6 (~CS)
RST: C13.1, CR1.2 (A), R15.1, R19.2, U20.30 (RST)
RSTCPU: U2.C9 (RESET), U4.20 (RSTCPU), U23.45 (RESET)
SBHE: ISA1.81 (SBHE), ISA3.81 (SBHE), ISA4.81 (SBHE), ISA5.81 (SBHE), ISA6.81 (SBHE), RP12.6 (R5), U15.12 (B6)
SEL0: R12.2, U4.119 (SEL0), U20.2 (SEL0)
SEL2: RP9.9 (R8), U4.117 (SEL2), U20.4 (SEL2)
SMEMR: ISA1.11 (~SMEMW), ISA2.11 (~SMEMW), ISA3.11 (~SMEMW), ISA4.11 (~SMEMW), ISA5.11 (~SMEMW), ISA6.11 (~SMEMW), RP12.2 (R1), U20.69 (~MEMR)
SMEMW: ISA1.12 (~SMEMR), ISA2.12 (~SMEMR), ISA3.12 (~SMEMR), ISA4.12 (~SMEMR), ISA5.12 (~SMEMR), ISA6.12 (~SMEMR), RP12.3 (R2), U20.70 (~MEMW)
SPKR: R34.1, U4.138 (SPK)
SYSRST: U3.L10 (RESET), U4.140 (SYSRST), U20.31 (SYSRST), U21.15 (I2b), U22.39 (RESET)
TBLED: J5.2, U20.42 (TURBOLED)
TC: ISA1.27 (TC), ISA2.27 (TC), ISA3.27 (TC), ISA4.27 (TC), ISA5.27 (TC), ISA6.27 (TC), U4.124 (TC)
TURBO: C14.1, J4.2, R17.2, U4.5 (TURBO), U20.39 (TURBO)
VCC: BC2.1, BC3.1, BC4.1, BC5.1, BC6.1, BC9.1, BC10.1, BC11.1, BC12.1, BC13.1, BC14.1, BC15.1, BC16.1, BC18.1, BC19.1, BC20.1, BC21.1, BC22.1, BC23.1, BC24.1, BC25.1, BC26.1, C9.1, C25.1, C26.1, C27.1, C28.1, CR1.1 (K), F1.1, ISA1.3 (+5V), ISA1.29 (VCC), ISA1.78 (+5V), ISA2.3 (VCC), ISA2.29 (VCC), ISA3.3 (+5V), ISA3.29 (VCC), ISA3.78 (+5V), ISA4.3 (+5V), ISA4.29 (VCC), ISA4.78 (+5V), ISA5.3 (+5V), ISA5.29 (VCC), ISA5.78 (+5V), ISA6.3 (+5V), ISA6.29 (VCC), ISA6.78 (+5V), J7.1 (+5V), J7.2 (+5V), J7.3 (+5V), J7.11 (+5V), J10.4, JP1.1, JP2.1, L5.1, Q2.1 (E), R9.2, R12.1, R16.1, R17.1, R18.2, R19.1, R21.1, R31.2, R32.2, RP1.1 (common), RP3.1 (common), RP4.1 (common), RP5.1 (common), RP6.1 (common), RP7.1 (common), RP9.1 (common), RP10.1 (common), RP11.1 (common), RP12.1 (common), RP13.1 (common), RP14.1 (common), SIM1.1 (VCC), SIM1.30 (VCC), SIM2.1 (VCC), SIM2.30 (VCC), SIM3.1 (VCC), SIM3.30 (VCC), SIM4.1 (VCC), SIM4.30 (VCC), SIM5.1 (VCC), SIM5.30 (VCC), SIM6.1 (VCC), SIM6.30 (VCC), SIM7.1 (VCC), SIM7.30 (VCC), SIM8.1 (VCC), SIM8.30 (VCC), U1.14 (VCC), U2.A1 (VCC), U2.A5 (VCC), U2.A7 (VCC), U2.A10 (VCC), U2.A14 (VCC), U2.C5 (VCC), U2.C12 (VCC), U2.D12 (VCC), U2.G2 (VCC), U2.G3 (VCC), U2.G12 (VCC), U2.G14 (VCC), U2.L12 (VCC), U2.M3 (VCC), U2.M7 (VCC), U2.M13 (VCC), U2.N4 (VCC), U2.N7 (VCC), U2.P2 (VCC), U2.P8 (VCC), U3.A6 (VCC), U3.A9 (VCC), U3.B4 (VCC), U3.E1 (VCC), U3.F1 (VCC), U3.F10 (VCC), U3.J2 (VCC), U3.J11 (CKM), U3.K3 (PULLUP), U3.K5 (VCC), U3.L4 (STEN), U3.L7 (VCC), U3.L9 (PULLUP), U5.7 (VCC), U6.1 (A14), U6.26 (A13), U6.28 (VCC), U10.28 (VCC), U11.28 (VCC), U12.28 (VCC), U13.28 (VCC), U14.20 (VCC), U15.20 (VCC), U16.20 (VCC), U17.20 (VCC), U18.28 (VCC), U19.5 (~SS), U19.25 (PROG), U19.26 (VCC), U19.40 (VCC), U20.41 (VCC), U20.91 (VCC), U22.5 (VCC), U22.6 (VCC), U22.11 (VCC), U22.19 (VCC), U22.26 (VCC), U22.30 (VCC), U22.33 (VCC), U22.34 (VCC), U22.38 (VCC), U22.54 (VCC), U22.64 (VCC), U22.70 (VCC), U22.71 (VCC), U22.75 (VCC), U22.76 (VCC), U23.2 (VCC), U23.16 (VCC), U23.22 (VCC), U23.34 (VCC), U23.49 (VCC), U23.54 (~FLT), U23.56 (VCC), U23.58 (VCC), U23.73 (VCC), U23.85 (VCC), U23.99 (VCC), U23.106 (VCC), U23.110 (VCC), U23.117 (VCC), U23.123 (VCC), U23.127 (VCC)
VDD: BC7.2, BC8.2, C15.1, C16.2, Q2.3 (C), R22.2, U4.45 (VCC), U4.53 (VCC), U4.78 (VCC), U4.102 (VCC), U4.115 (VCC), U4.149 (VCC), U4.173 (VCC), U4.195 (VCC), U9.14 (VDD)
WRKRDY: RP3.5 (R4), U4.203 (~WRKRDY)
W/R: U2.B10 (~W/R), U3.K4 (~W/R), U4.10 (~W/R), U22.28 (~W/R), U23.43 (~W/R)
X1CLK: U4.139 (OSC), U5.3 (X1), U20.32 (OSC), U21.13 (I1b)
XD0: ISA1.40 (DB0), ISA2.40 (DB0), ISA3.40 (DB0), ISA4.40 (DB0), ISA5.40 (DB0), ISA6.40 (DB0), RP14.9 (R8), U4.166 (SD0), U18.11 (D0), U19.12 (DB0)
XD1: ISA1.39 (DB1), ISA2.39 (DB1), ISA3.39 (DB1), ISA4.39 (DB1), ISA5.39 (DB1), ISA6.39 (DB1), RP14.8 (R7), U4.165 (SD1), U18.12 (D1), U19.13 (DB1)
XD2: ISA1.38 (DB2), ISA2.38 (DB2), ISA3.38 (DB2), ISA4.38 (DB2), ISA5.38 (DB2), ISA6.38 (DB2), RP14.7 (R6), U4.164 (SD2), U18.13 (D2), U19.14 (DB2)
XD3: ISA1.37 (DB3), ISA2.37 (DB3), ISA3.37 (DB3), ISA4.37 (DB3), ISA5.37 (DB3), ISA6.37 (DB3), RP14.6 (R5), U4.163 (SD3), U18.15 (D3), U19.15 (DB3)
XD4: ISA1.36 (DB4), ISA2.36 (DB4), ISA3.36 (DB4), ISA4.36 (DB4), ISA5.36 (DB4), ISA6.36 (DB4), RP14.5 (R4), U4.161 (SD4), U18.16 (D4), U19.16 (DB4)
XD5: ISA1.35 (DB5), ISA2.35 (DB5), ISA3.35 (DB5), ISA4.35 (DB5), ISA5.35 (DB5), ISA6.35 (DB5), RP14.4 (R3), U4.160 (SD5), U18.17 (D5), U19.17 (DB5)
XD6: ISA1.34 (DB6), ISA2.34 (DB6), ISA3.34 (DB6), ISA4.34 (DB6), ISA5.34 (DB6), ISA6.34 (DB6), RP14.3 (R2), U4.159 (SD6), U18.18 (D6), U19.18 (DB6)
XD7: ISA1.33 (DB7), ISA2.33 (DB7), ISA3.33 (DB7), ISA4.33 (DB7), ISA5.33 (DB7), ISA6.33 (DB7), RP14.2 (R1), U4.158 (SD7), U18.19 (D7), U19.19 (DB7)
XD8: ISA1.91 (D8), ISA3.91 (D8), ISA4.91 (D8), ISA5.91 (D8), ISA6.91 (D8), RP13.2 (R1), U4.157 (SD8)
XD9: ISA1.92 (D9), ISA3.92 (D9), ISA4.92 (D9), ISA5.92 (D9), ISA6.92 (D9), RP13.3 (R2), U4.156 (SD9)
XD10: ISA1.93 (D10), ISA3.93 (D10), ISA4.93 (D10), ISA5.93 (D10), ISA6.93 (D10), RP13.4 (R3), U4.155 (SD10)
XD11: ISA1.94 (D11), ISA3.94 (D11), ISA4.94 (D11), ISA5.94 (D11), ISA6.94 (D11), RP13.5 (R4), U4.154 (SD11)
XD12: ISA1.95 (D12), ISA3.95 (D12), ISA4.95 (D12), ISA5.95 (D12), ISA6.95 (D12), RP13.6 (R5), U4.153 (SD12)
XD13: ISA1.96 (D13), ISA3.96 (D13), ISA4.96 (D13), ISA5.96 (D13), ISA6.96 (D13), RP13.7 (R6), U4.152 (SD13)
XD14: ISA1.97 (D14), ISA3.97 (D14), ISA4.97 (D14), ISA5.97 (D14), ISA6.97 (D14), RP13.8 (R7), U4.151 (SD14)
XD15: ISA1.98 (D15), ISA3.98 (D15), ISA4.98 (D15), ISA5.98 (D15), ISA6.98 (D15), RP13.9 (R8), U4.150 (SD15)
ZWS: ISA1.8 (UNUSED), ISA2.8 (UNUSED), ISA3.8 (UNUSED), ISA4.8 (UNUSED), ISA5.8 (UNUSED), ISA6.8 (UNUSED), RP11.3 (R2), U4.135 (~ZWS)
pullup?: RP8.9 (R8), U20.97 (pullup?)
pullup??: RP9.3 (R2), U20.98 (pullup?)
